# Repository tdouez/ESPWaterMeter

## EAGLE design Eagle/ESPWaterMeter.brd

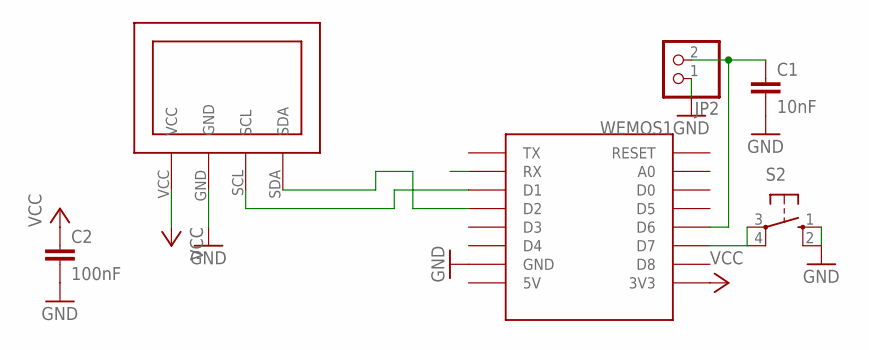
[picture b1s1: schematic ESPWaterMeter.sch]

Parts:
C1: 10nF; C025-025X050
C2: 100nF; C025-025X050
JP2: PINHD-1X2; 1X02
S2: 10-XX; B3F-10XX
U$2: OLED128X64
WEMOS1: WEMOS-D1-MINI

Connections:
GND: C1.2, C2.2, JP2.1, S2.1 (S), S2.2 (S1), U$2.GND, WEMOS1.GND
unnamed: U$2.SDA, WEMOS1.D2
unnamed: S2.3, S2.4 (P1), WEMOS1.D7
unnamed: C1.1, JP2.2, WEMOS1.D6
unnamed: U$2.SCL, WEMOS1.D1
VCC: C2.1, U$2.VCC, WEMOS1.3V3

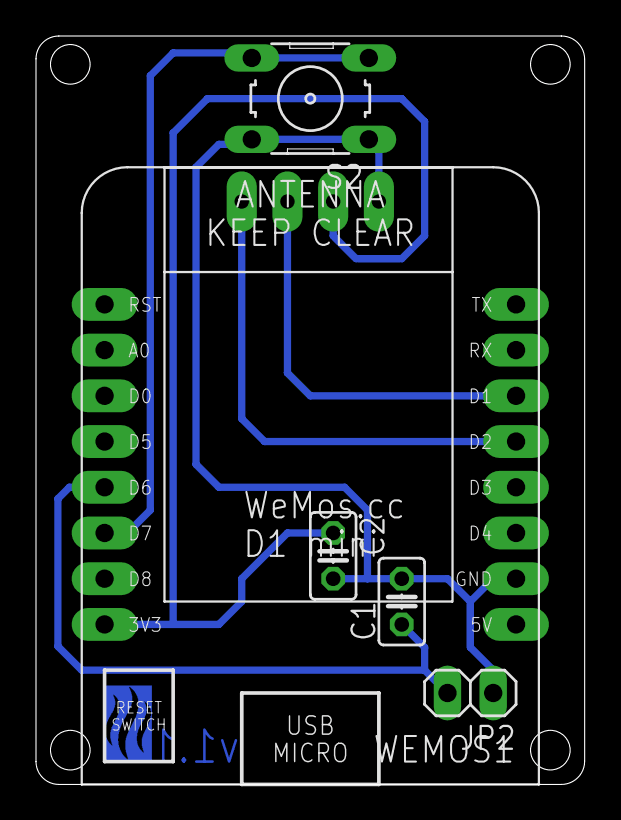
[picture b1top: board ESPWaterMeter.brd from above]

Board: 2 copper layers, 30.5 x 41.6 mm, 7 parts (1 on the bottom side), 6 nets.

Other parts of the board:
U$1: FB

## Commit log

2020-07-13 nt^p fix
2020-09-12 Update jquery.js
    Comment OTA options
2020-09-12 Comment OTA option
    Comment OTA option
2020-09-16 LittleFS implementation
    LittleFS implementation
2021-03-23 Bug fix on getDatewithDLS
    Bug fix on getDatewithDLS
    V1.02
2021-04-04 V1.03 - Add dates into index.html
    V1.03 - Add start and current date into index.html
2021-04-09 1.1.4 - Date fixbug and add timezone
    1.1.4 - Date fixbug and add timezone
2021-06-04 Update main.cpp
    Change volume/flow precision (2 digits after the decimal point)
2021-06-30 Bug fix on check continuous consumption
    Bug fix on check continuous consumption
2021-08-21 V1.07 - Bug fix on GMT and add histo memorization after reboot
    V1.07 - Bug fix on GMT and add histo memorization after reboot
2021-08-28 NTP fix
    NTP fix and add NTP config
2021-10-03 V1.09 - Change water sensor pin D4 to D6 and add POST request
    Change water sensor pin D4 to D6 and add POST request
2021-10-03 Add eagle files
2022-12-09 V1.1.0
    Change AsyncWiFiManager to ESPAsync_WiFiManager library
2022-12-20 Revert "V1.1.0"
    This reverts commit 5aff432f953c40fa34e0cb9237a83bd564ff897f.
2023-02-09 v1.0.10
    Bug fix ESPAsyncWiFiManager forgets data after reboot
